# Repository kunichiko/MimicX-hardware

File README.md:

# MimicX-hardware

**製品名: Mimic X** — 「Mimic X」プロジェクトのマイコン基板設計データ。

*Mimic X is an open-hardware USB-MIDI adapter family that lets a phone (or any
USB-MIDI / BLE-MIDI host) drive the real peripheral ports of 1980s Japanese
computers — the Sharp X68000 keyboard/mouse port and the ATARI-standard
9-pin joystick port, including Mega Drive 6-button pads. This repository holds
the board designs; the firmware, the protocol spec and the phone app live in the
sibling repositories linked at the bottom.*

- **Licence**: **CERN-OHL-S-2.0** (see [`LICENSE`](LICENSE)) — the `.ato`
  sources, the KiCad layouts and the docs are all modifiable sources.
  `tools/` is Apache-2.0. Vendor-supplied symbols, footprints and 3D models
  under `<board>/parts/` are third-party and are **not** covered; see
  [`NOTICE`](NOTICE) for the exact carve-out, the trademark terms and the
  datasheet policy.
- **MCU**: WCH **CH32X035G8U6** (QFN-28, RISC-V, 48 MHz, native USB 2.0 FS).
- **USB VID:PID**: `0x1209:0x9210` (Mimic X) and `0x1209:0x9211` (Mimic X
  Bridge), [requested from pid.codes](https://github.com/pidcodes/pidcodes.github.com/pull/1210).
- **Designed in [atopile](https://atopile.io)** — see
  [Design sources](#design-sources--回路図ファイルが無い理由) for why there is
  no `.kicad_sch` and where to read the circuit instead.

## 基板バリエーション / Boards

### `atari-joystick/` — ATARI / X68000 ジョイスティックアダプタ

D-SUB 9pin メス。X68000 / ATARI 標準ポートに直挿しし、メガドライブ 6 ボタン
パッドもエミュレートする。**rev 1.0.0、JLCPCB で製造済み。**

<p align="center"><sub>実装済みの基板と 3D プリントのケース (左) / KiCad レイアウトの 3D レンダ (右)。裏面と拡大は <a href="atari-joystick/README.md">基板 README</a> を参照</sub></p>

| | |
|---|---|
| ブロック図 / block diagram | [PDF](atari-joystick/docs/atari-joystick-block-diagram.pdf) · [SVG](atari-joystick/docs/atari-joystick-block-diagram.svg) |
| PCB レイヤープロット / layer plots | [PDF](atari-joystick/docs/atari-joystick-pcb.pdf) (silk / Cu / fab, 6 pages) |
| 対話的に眺める / browse the layout | [KiCanvas](https://kicanvas.org/?repo=https%3A%2F%2Fgithub.com%2Fkunichiko%2FMimicX-hardware%2Fblob%2Fmain%2Fatari-joystick%2Flayouts%2Fdefault%2Fdefault.kicad_pcb) |
| 回路の定義 / circuit source | [`atari_joystick.ato`](atari-joystick/atari_joystick.ato) |
| 製造データ / fabrication | [`layouts/default/production/`](atari-joystick/layouts/default/production) (Gerber + BOM + CPL) |
| 設計メモ / design notes | [`README.md`](atari-joystick/README.md) |

### `x68000-keyboard/` — X68000 キーボード / マウスアダプタ

ミニ DIN 7pin オス。X68000 のキーボード端子はマウス端子を兼用しており、本基板も
1 コネクタで両方をエミュレートする。4 層。**rev 1.0.0、JLCPCB で製造済み。rev 1.0.1 (外形のセンターずれ修正) は未発注。**

<p align="center"><sub>実装済みの基板と 3D プリントのケース (左) / KiCad レイアウトの 3D レンダ (右)。裏面と拡大は <a href="x68000-keyboard/README.md">基板 README</a> を参照</sub></p>

| | |
|---|---|
| ブロック図 / block diagram | [PDF](x68000-keyboard/docs/x68000-keyboard-block-diagram.pdf) · [SVG](x68000-keyboard/docs/x68000-keyboard-block-diagram.svg) |
| PCB レイヤープロット / layer plots | [PDF](x68000-keyboard/docs/x68000-keyboard-pcb.pdf) (silk / Cu ×4 / fab, 8 pages) |
| 対話的に眺める / browse the layout | [KiCanvas](https://kicanvas.org/?repo=https%3A%2F%2Fgithub.com%2Fkunichiko%2FMimicX-hardware%2Fblob%2Fmain%2Fx68000-keyboard%2Flayouts%2Fdefault%2Fdefault.kicad_pcb) |
| 回路の定義 / circuit source | [`x68000_keyboard.ato`](x68000-keyboard/x68000_keyboard.ato) |
| 製造データ / fabrication | [`layouts/default/production/`](x68000-keyboard/layouts/default/production) (Gerber + BOM + CPL) |
| 設計メモ / design notes | [`README.md`](x68000-keyboard/README.md) |

### `wireless-combo/` — 無線 (BLE-MIDI) Combined アダプタ

XIAO ESP32-C6 (BLE-MIDI ホスト) + CH32X035 (デバイスエンジン) の 2 チップ構成で、
ジョイスティックとキーボードの両ポートを 1 枚で担当する。ESP32 が CH32 の電源と
BOOT ピンを握っているため、CH32 のファームが壊れても SWD 経由で自力復旧できる。

> **rev 0.1 — 配線済み (4 層、DRC クリーン)、未発注。** 3D レンダと
> レイヤープロットはまだ置いていない。回路の全体像はブロック図と `.ato` を参照。

| | |
|---|---|
| ブロック図 / block diagram | [PDF](wireless-combo/docs/wireless-combo-block-diagram.pdf) · [SVG](wireless-combo/docs/wireless-combo-block-diagram.svg) |
| 回路の定義 / circuit source | [`wireless_combo.ato`](wireless-combo/wireless_combo.ato) |
| 設計メモ / design notes | [`README.md`](wireless-combo/README.md) |

## Design sources / 回路図ファイルが無い理由

この 3 基板はいずれも **[atopile](https://atopile.io) で設計している**。atopile は
回路を「図」ではなく「コード」で書く EDA で、`.ato` から直接ネットリストと KiCad
レイアウトを生成する。したがって **プロットできる回路図シート (`.kicad_sch`) は
そもそも存在しない**。回路を読むには次のいずれかを使う:

*These boards are designed in atopile, a text-based EDA: the circuit is written
as code and the netlist and KiCad layout are generated from it. There is no
schematic sheet to plot, so a reviewer has three ways in instead:*

1. **ブロック図 PDF** (`<board>/docs/*-block-diagram.pdf`) — 全ブロック、全信号、
   電源ドメイン、ピン割当表を 1 枚に収めた図。`tools/gen_block_diagrams.py` で
   生成しており、内容は `.ato` の記述と 1:1 で対応する。
   *The closest thing to a schematic: every block, every net that leaves a
   block, the power domains and the full pin map on one A4 sheet.*
2. **`.ato` ソース** — 部品・接続・値・設計理由がコメント付きで書かれている
   一次情報。`~` が接続、`~>` が直列挿入を表す。
   *The primary source, with the reasoning in the comments.*
3. **KiCad レイアウト** (`<board>/layouts/default/default.kicad_pcb`) — 上の表の
   KiCanvas リンクからブラウザで開ける。ネット名は `.ato` 側で
   `has_net_name` により意味のある名前 (`UP_3V3`, `KEY_TXD_3V3` など) に固定済み。
   *Browsable in KiCanvas; the nets carry meaningful names, not `Net-(U1-Pad3)`.*

ブロック図とレイヤープロットの再生成:

```sh
# ブロック図 (SVG + PDF)。PDF は headless Chrome で出力する
python3 tools/gen_block_diagrams.py

# PCB レイヤープロット
KC=/Applications/KiCad/KiCad.app/Contents/MacOS/kicad-cli
$KC pcb export pdf --mode-multipage \
   --layers F.Silkscreen,F.Cu,B.Cu,B.Silkscreen,F.Fab,Cmts.User \
   --common-layers Edge.Cuts \
   -o atari-joystick/docs/out atari-joystick/layouts/default/default.kicad_pcb
```

## 共通設計事項

- **MCU**: CH32X035G8U6 (QFN-28、48MHz、USB Full-Speed 内蔵)。**5V トレラント
  ではない** (絶対最大定格 VIN ≤ VDD+0.3V) ため、ターゲット機の 5V 信号とは
  必ずレベルシフタ (TC7MPB9307FT, パッシブ FET バススイッチ) を介して接続する
- **USB**: Type-C Receptacle、CC1/CC2 にそれぞれ 5.1kΩ プルダウン (Rd = sink/UFP)。
  CC は MCU の PC14/PC15 にも引いて内蔵 USB-PD コントローラで直接サンプリングする
- **電源**: USB バスパワー (VBUS 5V) を LDO (LP5907MFX-3.3) で 3.3V に降圧して MCU に
  供給する。CH32X035 の USB トランシーバ出力は VDD 直結なので、規格準拠ホストと
  正しく enumerate させるため VDD は必ず 3.3V にする。ターゲット機からの 5V は
  レベルシフタの B 側電源としてのみ使い、VBUS とは基板内で分離して逆流を防ぐ
- **デカップリング**: VDD ピンに 4.7µF + 0.1µF を近接配置
- **表示**: 電源 LED (緑 0603、常時点灯) + フルカラー LED (WS2812B-2020、
  DI 直前に 470Ω 直列ダンピング抵抗)。atari-joystick 以外の基板は 3.3V 給電が
  定格内の同外形品 WS2812B-2020-V6 (C52917434) に置き換え済み
- **書き込み**: BOOT ボタンで PC17 (USB D+) を 4.7kΩ 経由で HIGH に引き上げた状態で
  リセットすると、WCH の USB DFU ブートローダに入る

## 関連リポジトリ / Related repositories

- [MimicX-app](https://github.com/kunichiko/MimicX-app) — Flutter アプリ (USB-MIDI / BLE-MIDI ホスト)
- [MimicX-firmware](https://github.com/kunichiko/MimicX-firmware) — マイコンファームウェア (CH32X035 / ESP32)
- [MimicX-protocol](https://github.com/kunichiko/MimicX-protocol) — USB-MIDI 通信プロトコル仕様

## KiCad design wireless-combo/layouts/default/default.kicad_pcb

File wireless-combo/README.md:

# MimicX Wireless Combo Adapter (XIAO ESP32-C6 + CH32X035)

*BLE-MIDI wireless Combined adapter: an ESP32-C6 takes MIDI in over BLE or USB
and relays it to a CH32X035 device engine over I2C, driving both retro ports
from one board. **Board rev 0.1 — routed (4-layer, DRC clean), not yet
fabricated**; renders and layer plots are not here yet. Designed in
[atopile](https://atopile.io); the circuit lives in
[`wireless_combo.ato`](wireless_combo.ato).*

- **ブロック図 / block diagram**:
  [PDF](docs/wireless-combo-block-diagram.pdf) ·
  [SVG](docs/wireless-combo-block-diagram.svg)
- **USB VID:PID**: `0x1209:0x9211` (Mimic X Bridge — 無線側は ESP32 が USB
  デバイスとして見えるため、有線 2 基板とは別 PID)

BLE-MIDI 無線対応の Combined アダプタ。1 枚の基板に

- **Seeed XIAO ESP32-C6** — BLE-MIDI ホスト / CH32 の自動 OTA (SWD) / 電源・BOOT 制御
- **CH32X035G8U6** — デバイスエンジン (`combined-i2c` ファーム)
- **2x5 ボックスヘッダ** — フラットケーブル経由で D-SUB 9pin (ATARI / X68000 / MD ジョイスティック)
- **2x4 ボックスヘッダ** — フラットケーブル経由で Mini DIN 7pin (X68000 キーボード / マウス / REMOTE)
- **JST XH 3P** — WCH-LinkE 用 SWD デバッグ端子 (保険)
- **M3 ネジ穴 ×4** — メッキ穴、GND 接続 (ケース固定用)

D-SUB / Mini DIN は基板直付けせず、2.54mm ボックスヘッダ (逆挿し不可) 経由の
汎用フラットケーブル接続とする。2x5 側は IDC 圧着型 D-SUB 9pin をそのまま
圧着したケーブルが使える配列にしてある。

を搭載する。ファームウェアは既存の 2 チップ構成 (protocol §2.5) をそのまま使う:
CH32 側 = `MimicX-firmware/platforms/ch32x035` の `combined-i2c` env、
ESP32 側 = `MimicX-firmware/platforms/esp32c6` (内包イメージを `mimic-x-combo` に設定)。

## ブロック図

```
                USB-C (給電 + 書込/ログ)
                   │
  ┌────────────────┴───┐        VDD33 (常時)
  │  XIAO ESP32-C6     │3V3 ──┬─────────────┐
  │                    │      │             S│
  │ D0: CH32_PWR_OFF ──┼──────┼──────────── G│Q1 AO3401A (default ON)
  │ D1: CH32_BOOT ─────┼─4.7k─┼─┐           D│
  │ D3: CH32_INT ──────┼──┐   │ │   VDD_SW ──┴─┬──[10k]── GND (ブリーダ)
  │ D4: SDA_SWDIO ─────┼─┐│   │ │      │       │
  │ D5: SCL_SWCLK ─────┼┐││ [pull-ups 4.7k/10k は VDD_SW へ]
  └────────────────────┘│││   │ │      │
                        │││   │ │  ┌───┴──────────┐    ┌─ TC7MPB9307FT ─ D-SUB9
             PC19/SCL ──┘││   │ └──│ PC17 (BOOT)  │────┤   (VCCB = D-SUB Pin5)
             PC18/SDA ───┘│   │    │  CH32X035    │    │
             PB1/INT ─────┘   │    │ combined-i2c │    └─ TC7MPB9307FT ─ MiniDIN7
                              │    │   PB0 ─ WS2812B    (VCCB = DIN Pin1 Vcc2)
              BOOTボタン ─4.7k┴────│              │
                                   └──────────────┘
```

## この基板の設計肝: ESP32 による CH32 の電源 / BOOT 制御

既存構成の弱点は「CH32 ファームが起動直後に SDI (SWD) を無効化するため、
I2C が死ぬと SWD でも復旧できない半ブリック状態が生じる」こと (実事例あり)。
本基板は WCH ISP ブートローダが SDI を有効のまま残すこと (実機検証済み) を
利用し、ESP32 の GPIO 2 本で **どんなファーム状態からでも** 復旧できる:

| XIAO ピン | GPIO | 機能 | 極性 |
|---|---|---|---|
| D0 | GPIO0 | `CH32_PWR_OFF` — Q1 ゲート | High=電源OFF (100k PD でデフォルトON) |
| D1 | GPIO1 | `CH32_BOOT` — 4.7k 経由で PC17(UDP) | POR 時 High=ブートローダ突入 |
| D3 | GPIO21 | `CH32_INT` (既存) | active-low, 10k PU→VDD_SW |
| D4 | GPIO22 | `SDA_SWDIO` (既存) | 4.7k PU→VDD_SW |
| D5 | GPIO23 | `SCL_SWCLK` (既存) | 4.7k PU→VDD_SW |

### 復旧シーケンス (ESP32 ファームに実装する)

```
1. SDA/SCL/INT/BOOT を Low 出力 or プルなし Hi-Z にする
   (OFF 中に 1 本でも High があると保護ダイオード経由のバックフィードで
    POR がかからない。プルアップ類を VDD_SW に繋いでいるのも同じ理由)
2. CH32_PWR_OFF = High → 100ms 待つ (10k ブリーダで VDD_SW 放電)
3. CH32_BOOT = High
4. CH32_PWR_OFF = Low → POR。PC17=High でブートローダ突入 (SDI 有効)
5. ~50ms 後 CH32_BOOT = Low (書込後の ndmreset でアプリ起動させるため)
6. 即 SWD 書込 (ブートローダのタイムアウト前に halt すれば以降は安全)
```

`ch32_ota.c` の SWD 失敗時フォールバックとしてこのシーケンスを足せば、
ENTER_SWD ハンドオフ (CH32 ファームの協力前提) に依存しない自己修復になる。

## 電源設計

5V 電源は 3 系統あり、**どれか 1 つでも供給されていれば動作する**:

```
USB-C (XIAO) ──────────────────┬── VCC_ESP (5V 幹線 = XIAO 5V ピン)
VCC_JOY (D-SUB Pin5) ─▶|B5819W─┤        │ XIAO 内蔵 LDO
VCC_KBD (DIN Pin1)   ─▶|B5819W─┘        ▼
                                      VDD33 (3.3V 常時系)
                                        │ Q1 (P-FET)
                                        ▼
                                      VDD_SW (CH32 サブシステム)
```

- XIAO の 3V3 ピンは内蔵 LDO の**出力** (入力不可)。USB 未接続時はホスト 5V を
  ショットキー経由で 5V ピン (VBUS) に注入して XIAO を駆動する (Seeed 公式推奨方式)
- 回路全体の 3.3V は XIAO 内蔵 LDO 出力 (`VDD33`) を使う。CH32 サブシステムの
  追加負荷は最悪 ~60mA 程度 (CH32 ~10mA + WS2812 ≤45mA + プルアップ) で、
  ESP32 自身の無線ピークを賄う前提の内蔵レギュレータの範囲内。
  ノイズや電流に不安が出た場合は VCC_ESP → 外付け 3.3V レギュレータで
  ESP32 以外の 3.3V を分離する代替案あり (既存基板の LP5907MFX-3.3 は 250mA で
  この用途には十分。ただし ESP32 本体は駆動できない点に注意)
- B5819W (SOD-123, LCSC C8598) の Vf は 0.3A 付近で 0.4V 台 → ホスト給電時 VCC_ESP ≈ 4.5〜4.6V。ダイオードにより
  VCC_JOY / VCC_KBD は相互に直結されず、USB VBUS からホストへの逆流もない
- ホスト給電時は ESP32 の無線 TX バースト (数百 mA) がレトロ機のポート給電に
  乗る。VCC_ESP に 22µF バルクを置いて平滑しているが、**ホスト側ポートの
  給電能力 (ヒューズ/許容電流) は実機で要確認**
- CH32 サブシステム (CH32 / WS2812 / プルアップ / レベルシフタ VCCA) は
  すべて `VDD_SW` (Q1 スイッチド)。**このレールに載せ忘れた常時系プルアップが
  1 本でもあると電源 OFF 復旧が壊れる**ので、変更時は要注意
- レベルシフタ B 側 (5V) はホスト給電: `VCC_JOY` (D-SUB Pin5) と
  `VCC_KBD` (DIN Pin1 Vcc2) を各コネクタから直接取る
- CH32 の USB は未接続 (PC16 = NC, PC17 = BOOT 制御専用)。最終復旧手段も
  ESP32 経由の BOOT+SWD で代替できるため、wchisp 用 USB は設けない

## ケーブル配線 (ヘッダ Pin n = フラットケーブルの芯線 n)

専用の[変換基板](#変換基板-atari-joystick-bo--x68000-keyboard-bo)を使う場合は、両端とも IDC ソケットを
同じ向き (1 番線 = ▽ 側) に圧着したストレートケーブルでつなぐ。以下は変換基板を
使わずにケーブル側で直接コネクタを付ける場合の対応表。

| 2x5 (J: joystick) | D-SUB 9pin | | 2x4 (J: keyboard) | Mini DIN 7pin |
|---|---|---|---|---|
| 1 | 1 Up | | 1 | 1 Vcc2 (+5V) |
| 2 | 6 TRIG-A | | 2 | 2 MSDATA |
| 3 | 2 Down | | 3 | 3 KEY RxD |
| 4 | 7 TRIG-B | | 4 | 4 KEY TxD |
| 5 | 3 Left | | 5 | 5 READY |
| 6 | 8 COMMON / TH | | 6 | 6 REMOTE |
| 7 | 4 Right | | 7 | 7 GND (シールドもここへ) |
| 8 | 9 GND | | 8 | GND (予備) |
| 9 | 5 +5V (ホスト給電) | | | |
| 10 | GND (D-SUB 側は未接続) | | | |

- **ジョイスティック**: 10 芯フラットケーブルの片側に 2x5 IDC ソケット、反対側に
  **IDC 圧着型 D-SUB 9pin メス** を (1 番線 = D-SUB Pin1 に合わせて) 圧着するだけ
  でよい。IDC D-SUB は芯線を 1→1, 2→6, 3→2 … と上下段に交互に振り分けるため、
  上表のヘッダ配列になっている (PC のシリアルポート用ブラケットケーブルと同じ
  "AT/Intel" 配列)。10 番線 (基板側 GND) は D-SUB 側で未接続
- **キーボード**: IDC 圧着型の Mini DIN は無いので、8 芯フラットケーブルの片側に
  2x4 IDC ソケットを圧着し、反対側は芯線 1〜7 を DIN プラグの同番ピンへ手配線する。
  DIN シールドは**ケーブル側コネクタの根元で GND (7 番線) に合流**させる
- 10P ソケットは 8P ヘッダに入らないが、8P ソケットは 10P ヘッダのシュラウドに
  片寄せで入ってしまう場合があるので、ケーブルにはラベルを付けておく
- 基板側: 2x5 ボックスヘッダ BOOMELE 2.54-2\*5P = LCSC C5665、
  2x4 ボックスヘッダ BOOMELE 2.54-2\*4P = LCSC C9135

## 変換基板 (atari-joystick-bo / x68000-keyboard-bo)

フラットケーブルの先に付ける受動基板。同じ atopile プロジェクトの別ビルドとして
持ち、ボックスヘッダは親基板と同じ `parts/idc_connectors.ato` の定義を使う
(ピン配置が親子で食い違わない)。ビルド名の `-bo` は breakout の略。将来ほかの
ジョイスティックや機種 (PC-98 キーボードなど) 用を足せるよう、対象機の名前を前に付けている。

| ビルド | エントリ | レイアウト | 構成 | 形状 |
|---|---|---|---|---|
| `atari-joystick-bo` | [`atari_joystick_bo.ato`](atari_joystick_bo.ato) | `layouts/atari-joystick-bo/` | J1: 2x5 ボックスヘッダ (C5665) / J2: ハンダカップ型 D-SUB 9pin メス用エッジパッド (手はんだ) | atari-joystick-slim 形 35 × 16 mm |
| `x68000-keyboard-bo` | [`x68000_keyboard_bo.ato`](x68000_keyboard_bo.ato) | `layouts/x68000-keyboard-bo/` | J1: 2x4 ボックスヘッダ (C9135) / J2: Mini DIN 7pin オス (手はんだ) | x68000-keyboard 形 (本体 20.6 × 12.2 mm) |

- どちらも 2 層、厚さ **1.6 mm** (D-SUB のハンダカップ列の間に入る厚み)
- コネクタ側は元の基板と同寸 (atari-joystick-bo: 先端 10 mm のエッジパッドと M2.6 用
  φ2.8 穴 ×2、x68000-keyboard-bo: ネックと Mini DIN まわり)。ボックスヘッダを載せるため
  後ろ側を延長してある (atari-joystick-bo +5 mm、x68000-keyboard-bo +6.4 mm)
- D-SUB の取り付け方は [atari-joystick-slim の README](../atari-joystick-slim/README.md#d-sub-9pin-の取り付け) と同じ
- 状態: 配線済み、未発注

### SWD デバッグ端子 (XH 3P, B3B-XH-A = LCSC C144394)

WCH-LinkE でのデバッグ / 強制書き換え用の保険。PC18/PC19 は I2C/SWD 兼用線
なので実体は I2C バスのタップ。
**通常は未実装** (BOM / CPL から除外済み)。使うときだけ B3B-XH-A を手はんだする。

| XH 3P | 信号 |
|---|---|
| 1 | SWCLK (= SCL, CH32 PC19) |
| 2 | SWDIO (= SDA, CH32 PC18) |
| 3 | GND |

使用時の注意:
- ESP32 が同じ線を駆動するため、**WCH-LinkE 使用中は ESP32 を静かにしておく**
  (リセット保持、または I2C/OTA が走っていないタイミングで)
- 通常稼働中の CH32 は SDI off なので、**BOOT ボタン + 電源再投入でブート
  ローダ (SDI 有効) にしてから**繋ぐと確実

## 実装前 TODO

- [ ] `parts/XIAO_ESP32C6/` のフットプリントは**仮置き** (2.54mm ピッチ /
      列間 15.24mm)。Seeed 公式の機械図面と照合して確定させる
- [ ] `parts/AO3401A_SOT23/` の SOT-23 ランド、`parts/B5819W_SOD123/` の SOD-123 ランド (KiCad 標準)、
      `parts/JST_XH_B3B/` の XH ランドを
      データシート推奨値と照合
- [ ] 信号ラインの TVS (SP3012-04UTG 等) 追加検討 — ケーブル化で配線が伸びる
      ため既存基板より優先度高
- [ ] 10kΩ / 100kΩ 抵抗は初回 `ato build` 時に LCSC ピッカーが解決する
      (ネットワーク必要)。他はローカル parts/ キャッシュで完結
- [ ] ESP32 ファームに `CH32_PWR_OFF` / `CH32_BOOT` の制御と復旧フォール
      バックを実装 (`board_config.h` に BOARD_CH32_PWR_GPIO=0 /
      BOARD_CH32_BOOT_GPIO=1 を追加)

## ビルド

```sh
cd MimicX-hardware/wireless-combo
~/.local/bin/ato build --keep-picked-parts               # 3 基板すべて
~/.local/bin/ato build --keep-picked-parts -b atari-joystick-bo   # 1 基板だけ (default / atari-joystick-bo / x68000-keyboard-bo)
```

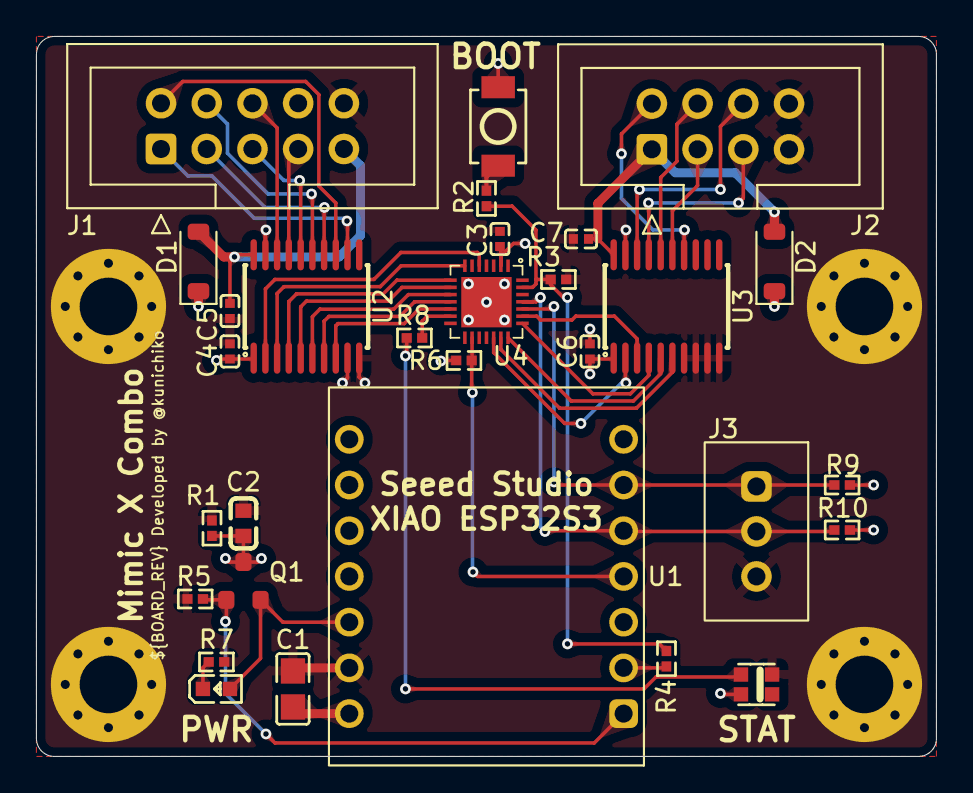
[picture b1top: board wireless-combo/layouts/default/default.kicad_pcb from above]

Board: 4 copper layers, 50.0 x 40.0 mm, 34 parts (0 on the bottom side), 40 nets.

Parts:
C1: 22µF ±20%; C0805
C2: 4.7µF ±10%; C0603
C3, C4, C5, C6, C7: 100nF ±10%; C0402
D1, D2: B5819W_SOD123
H1, H2, H3, H4: MountingHole_M3
J1: IDC_Header_2x05
J2: IDC_Header_2x04
J3: JST_XH_B3B
LED1: LED0603-RD
LED2: LED-SMD_4P-L2.2-W2.0-P1.00_WS2815C-2020-4P
Q1: AO3401A_SOT23
R1, R6: 10kΩ ±1%; R0402
R2, R4, R9, R10: 4.7kΩ ±1%; R0402
R3, R5: 100kΩ ±1%; R0402
R7: 1kΩ ±1%; R0402
R8: 470Ω ±1%; R0402
SW1: SW-SMD_L3.9-W3.0-P4.45
U1: XIAO_ESP32C6
U2, U3: TSSOP-20_L6.5-W4.4-P0.65-LS6.5-BL
U4: QFN-28_L4.0-W4.0-P0.40-BL-EP2.8

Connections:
CH32_BOOT: R4.1, U1.2
CH32_INT: R6.2, U1.4, U4.16
CH32_PWR_OFF: Q1.1, R5.1, U1.1
COMMON_3V3: U2.2, U4.5
DOWN_3V3: U2.6, U4.10
GND: C1.2, C2.2, C3.2, C4.2, C5.2, C6.2, C7.2, H1.1, H2.1, H3.1, H4.1, J1.8, J1.10, J2.7, J2.8, J3.3, LED2.2, R1.2, R3.2, R5.2, R7.2, U1.13, U2.9, U2.10, U2.19, U3.7, U3.8, U3.9, U3.10, U3.19, U4.29
KEY_RXD_3V3: U3.5, U4.21
KEY_TXD_3V3: U3.4, U4.22
LEFT_3V3: U2.4, U4.8
MSDATA_3V3: U3.6, U4.20
PB0: R8.1, U4.13
READY_3V3: U3.3, U4.23
REMOTE_3V3: U3.2, U4.19
RIGHT_3V3: U2.3, U4.7
SCL_SWCLK: J3.1, R9.2, U1.6, U4.24
SDA_SWDIO: J3.2, R10.2, U1.5, U4.25
TRIGA_3V3: U2.7, U4.11
TRIGB_3V3: U2.5, U4.9
UP_3V3: U2.8, U4.12
VCC_ESP: C1.1, D1.1, D2.1, U1.14
VCC_JOY: C5.1, D1.2, J1.9, U2.20
VCC_KBD: C7.1, D2.2, J2.1, U3.20
VDD33: LED1.2, Q1.2, U1.12
VDD_SW: C2.1, C3.1, C4.1, C6.1, LED2.4, Q1.3, R1.1, R6.1, R9.1, R10.1, SW1.1, U2.1, U3.1, U4.2
cathode: LED1.1, R7.1
common: J1.6, U2.18
din: LED2.3, R8.2
down: J1.3, U2.14
key_rxd: J2.3, U3.15
key_txd: J2.4, U3.16
left: J1.5, U2.16
msdata: J2.2, U3.14
ready: J2.5, U3.17
remote: J2.6, U3.18
right: J1.7, U2.17
terminal_b: R2.1, SW1.2
triga: J1.2, U2.13
trigb: J1.4, U2.15
up: J1.1, U2.12
usb_dp: R2.2, R3.1, R4.2, U4.27

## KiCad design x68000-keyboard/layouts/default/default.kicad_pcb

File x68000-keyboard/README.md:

# x68000-keyboard

Mimic X — X68000 キーボードアダプタ基板 (キーボード + マウス相乗り対応)

*USB-MIDI to Sharp X68000 keyboard/mouse port adapter (mini-DIN 7P, 4-layer
board). Board rev 1.0.0 fabricated at JLCPCB; rev 1.0.1 (outline centering fix)
not yet ordered. Designed in
[atopile](https://atopile.io) — the circuit lives in
[`x68000_keyboard.ato`](x68000_keyboard.ato), not in a schematic sheet.*

<p align="center"><sub>実装済みの基板と 3D プリントのケース (背景はカッティングマット)</sub></p>

<p align="center"><sub>KiCad レイアウトの 3D レンダ (部品面 / はんだ面)</sub></p>

- **ブロック図 / block diagram**:
  [PDF](docs/x68000-keyboard-block-diagram.pdf) ·
  [SVG](docs/x68000-keyboard-block-diagram.svg) — 全ブロック・全信号・電源
  ドメイン・ピン割当を 1 枚に収めた図
- **PCB レイヤープロット / layer plots**:
  [PDF](docs/x68000-keyboard-pcb.pdf) (silk / Cu ×4 / fab, 8 pages)
- **レイアウトをブラウザで**:
  [KiCanvas](https://kicanvas.org/?repo=https%3A%2F%2Fgithub.com%2Fkunichiko%2FMimicX-hardware%2Fblob%2Fmain%2Fx68000-keyboard%2Flayouts%2Fdefault%2Fdefault.kicad_pcb)
- **製造データ**: [`layouts/default/production/`](layouts/default/production)
  (Gerber + BOM + CPL, JLCPCB 発注そのまま)
- **USB VID:PID**: `0x1209:0x9210`

## 用途

スマートフォン (USB-MIDI ホスト) から CH32X035 経由で、X68000 のキーボード
信号 (KEY TxD/RxD) およびマウス信号 (MSDATA) を生成し、X68000 本体の
ミニ DIN 7pin ポートに接続して使用する。

X68000 のキーボードコネクタは **マウス端子を兼用** しており、本基板も
1 つのコネクタで両方をエミュレートする (ファーム `BOARD_X68K_FULL`)。

## 主要部品

| 部品 | 型番 / 仕様 | 備考 |
|------|-----------|------|
| MCU | WCH CH32X035G8U6 | QFN28、48MHz、USB Full-Speed 内蔵、3.3V 駆動 |
| USB コネクタ | USB Type-C (Receptacle, 16pin) | スマートフォンと接続 |
| 出力コネクタ | Mini DIN 7pin オス (自作 `MiniDIN_7P_X68000`) | X68000 キーボード端子 (手配コネクタを基板に直付け) |
| LDO | LP5907MFX-3.3 (250 mA) | VBUS 5V → MCU VDD 3.3V |
| レベルシフタ | Toshiba TC7MPB9307FT (TSSOP-20) | 8-bit Dual-Supply Bus Switch、3.3V↔5V |
| BOOT ボタン | XUNPU TS-1088-AR02016 (3.9×3.0mm, 2 ピン) | リセット時 USB DFU 起動用 |
| その他 | デカップリング 0.1µF / 4.7µF, USB Type-C CC 抵抗 5.1kΩ ×2 |

> 基板上の状態表示は **電源 LED (緑 0603, 常時点灯)** と **フルカラー LED
> (WS2812B-2020-V6, シリアル制御 RGB)** の 2 個。PB3 / PB4 は引き続き未使用。

## ピン割当 (CH32X035G8U6 QFN28 → コネクタ)

> **注意 (重要)**: 旧版 README には `PA15–PA19` という記載があったが、これは
> CH32X035 別パッケージ (LQFP48 など) のピン名で、MimicX で採用している
> **CH32X035G8U6 (QFN28) には存在しない**。詳細は `../docs/CH32X035.md` §3 参照。
> 以下が QFN28 の実ピンに合わせた最新割当。

| QFN28 Pin | MCU 信号 | レベルシフタ | DIN 7pin | 方向 (MCU 視点) | 用途 |
|---:|---|---|---:|---|---|
| 22 | PB11 (USART1_RX, RX1_2) | a6↔b6 | Pin 4 (KEY TxD) | **IN** | X68000 本体からのコマンド受信 (2400/8N1) |
| 21 | PB10 (USART1_TX, default) | a4↔b4 | Pin 3 (KEY RxD) | **OUT** | キーコード送信 (2400/8N1) |
| 23 | PB12 (GPIO 入力) | a5↔b5 | Pin 5 (READY) | IN | 1=ホスト準備完了、Low 時送信抑止 |
| 20 | PB9 (USART4_TX, TX4_3) | a8↔b8 | Pin 2 (MSDATA) | OUT | マウスデータ送信 (4800/8N2) |
| 19 | PB8 (GPIO) | a7↔b7 | Pin 6 (REMOTE) | (FW 依存) | TV リモコン信号。用途は将来検討 |
| 13 | PB0 | — | — | OUT | フルカラー LED (WS2812B-2020-V6) DI 駆動。470Ω 直列ダンピング抵抗経由 |
| 14 | PB3 | — | — | — | 未使用 |
| 15 | PB4 | — | — | — | 未使用 |
| —  | (GND) | — | Pin 7 | — | 共通 GND |
| —  | (VCC2) | (B 側 VCCB) | Pin 1 (Vcc2 +5V) | — | X68000 本体の +5V をレベルシフタ B 側電源として受け入れ |

USART のリマップ設定 (`AFIO_PCFR1`):
- `USART1` は PB10/PB11 を使うため `USART1_REMAP` ビットの設定で
  `RX1_2` (= PB11) にマップする必要がある。
- `USART4` は PB9 の `TX4_3` リマップを使用 (MSDATA は送信のみで RX は不要)。

詳細はファームウェア `MimicX-firmware/src/functions/x68k_keyboard/` および
`x68k_mouse/` 参照。

## DIN ピン名の方向解釈 (重要)

X68000 サービスマニュアル上の `KEY TxD` / `KEY RxD` は **X68000 本体 (ホスト) 視点**
で命名されている:

| Pin | ラベル | データの流れ | MCU (= キーボード側) の動作 |
|----:|---|---|---|
| 3 | KEY RxD | ホストが**受信** ← キーボード | MCU は**送信** (TX) |
| 4 | KEY TxD | ホストが**送信** → キーボード | MCU は**受信** (RX) |

UART の一般則「片側の Tx は相手側の Rx に繋ぐ」を素直に適用すれば良い:
- ホストの TxD (Pin 4) → MCU の RX1 (PB11)
- ホストの RxD (Pin 3) ← MCU の TX1 (PB10)

## ミニ DIN 7pin (本体側 = メス、当基板側 = オス)

```
       _______
      /  4 3  \         (DIN 7pin Male, looking at the plug from outside)
     | 7  6  5 |
      \_2 1__/
```

本基板は **ユーザ手配のコネクタを直接はんだ付け** する想定で、フットプリントは
自作 (`parts/MiniDIN_7P_X68000/MiniDIN_7P_X68000.kicad_mod`) を採用している。
コネクタの実寸 (Hirose HMD-7P 系を想定) に合わせて KiCad の Footprint Editor
で本実装済み。差し替える場合は同ファイルを編集して `ato build` を再実行する。
X68000 サービスマニュアル準拠のピン配置:

| Pin | 信号 | 当基板での扱い |
|-----|------|---|
| 1 | Vcc2 (+5V) | レベルシフタ B 側 VCCB に接続 (X68000 から給電) |
| 2 | MSDATA (キーボード→本体) | MCU PB9 ← レベルシフタ |
| 3 | KEY RxD (キーボード→本体) | MCU PB10 (TX1) ← レベルシフタ |
| 4 | KEY TxD (本体→キーボード) | MCU PB11 (RX1) ← レベルシフタ |
| 5 | READY (本体→キーボード) | MCU PB12 ← レベルシフタ |
| 6 | REMOTE (TV リモコン用) | MCU PB8 ← レベルシフタ |
| 7 | GND | 共通 GND |

## 信号レベルとバッファ

- すべて **5V TTL**
- CH32X035 は **5V トレラントではない** (絶対最大定格 VIN ≤ VDD+0.3V =
  3.6V at VDD=3.3V)。詳細は `../docs/CH32X035.md` §5・§7 参照。
- そのため X68000 側 5V 信号と接続する全 5 ラインに **Toshiba TC7MPB9307FT
  (8 ch パッシブ FET バススイッチ、TSSOP-20)** を介す。
  - VCCA = VDD33 (3.3V、MCU 側) / VCCB = VCC2 (5V、X68000 本体の Vcc2) / OE = GND 固定
  - チャネル 4〜8 を使用 (a4/a5/a6/a7/a8)、未使用の 1〜3 は A 側を GND に落としてフローティング回避
- パッシブ FET 型 (FET パススルー) を選定する理由は ATARI アダプタと同じで、
  X68000 ホスト側 8255 + プルアップとの相性を考慮したもの。`../docs/CH32X035.md`
  §7 参照。

## 電源

本基板は **2 系統の電源** を用途別に取り込む構成:

| レール | 供給元 | 用途 |
|---|---|---|
| **VBUS (5V)** | USB Type-C (スマホ等のホスト) | LDO で 3.3V に降圧して MCU と レベルシフタ A 側 (VCCA) を駆動 |
| **VDD33 (3.3V)** | LDO (LP5907MFX-3.3) | MCU 本体・LDO 後段デカップリング |
| **VCC2 (5V)** | X68000 本体 DIN Pin 1 (Vcc2) | レベルシフタ B 側 (VCCB) — 5V 信号レベル基準と同電位を取る |

ポイント:
- VBUS と Vcc2 は基板上で **直接接続しない** (それぞれ別のレールとして分離)。
  逆流・逆給電のリスクが無くなる。
- レベルシフタ B 側電源を X68000 側 5V (Vcc2) から取ることで、ホスト側信号
  レベルと完全に整合する (ホストが電源断のときは B 側も電位がなくなるので、
  バススイッチが自然と high-Z 状態になる)。
- MCU 動作には USB 接続が必須 (スマホからのバスパワー 5V → LDO で 3.3V)。
  X68000 単体で電源を取って動作させたい場合は本構成では非対応。

## レイアウトのヒント

- USB Type-C コネクタは基板の一辺に
- ミニ DIN 7pin は反対側エッジ。X68000 本体への取り回しを想定して
  ケーブル方向を考える
- QFN28 周りはデカップリング (4.7µF + 0.1µF) を近接配置
- USB 信号 (DP/DM) は 90Ω 差動でルーティング
- KEY TxD / KEY RxD / MSDATA / READY / REMOTE は 1 つの DIN コネクタに
  集約、ESD 保護 (TVS) を入れることを推奨 (TODO)

## 参考

- USB Type-C CC 1/2 ピンには 5.1kΩ プルダウン (VBUS / Source 認識のため必須)
- READY は X68000 起動時にしばらく Low のままなので、送信キューを内部に持つ
  実装を前提 (FW 側で対応済み)
- マウス機能を別基板に分けたい場合は、`functions/x68k_mouse/` を外して
  USART4 関連回路を不実装にし、コネクタも MSDATA を未配線にできる
- REMOTE (Pin 6) は X68000 純正キーボード上の TV リモコン受光部信号。
  当基板では PB8 GPIO に接続しておくだけで、用途は将来 FW 側で検討する

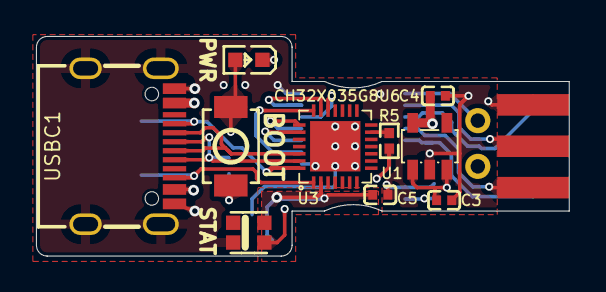
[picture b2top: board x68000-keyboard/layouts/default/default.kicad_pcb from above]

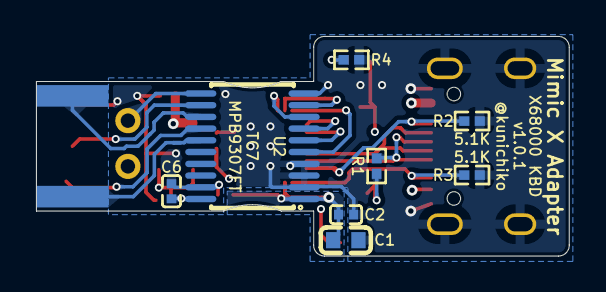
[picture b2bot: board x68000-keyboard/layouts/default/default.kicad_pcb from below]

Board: 4 copper layers, 29.6 x 12.2 mm, 19 parts (8 on the bottom side), 22 nets.

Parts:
C1: 4.7µF ±10%; C0603
C2, C5, C6: 100nF ±10%; C0402
C3, C4: 1µF ±10%; C0402
J1: MiniDIN_7P_X68000
LED1: LED0603-RD
LED2: LED-SMD_4P-L2.2-W2.0-P1.00_WS2815C-2020-4P
R1: 4.7kΩ ±1%; R0402
R2, R3: 5.1kΩ ±1%; R0402
R4: 1kΩ ±1%; R0402
R5: 470Ω ±1%; R0402
SW1: SW-SMD_L3.9-W3.0-P4.45
U1: SOT-23-5_L3.0-W1.7-P0.95-LS2.8-BR
U2: TSSOP-20_L6.5-W4.4-P0.65-LS6.5-BL
U3: QFN-28_L4.0-W4.0-P0.40-BL-EP2.8
USBC1: USB-C_SMD-TYPE-C-31-M-12_1

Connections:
GND: C1.2, C2.2, C3.2, C4.2, C5.2, C6.2, J1.7, LED2.2, R2.2, R3.2, R4.2, U1.2, U2.2, U2.3, U2.4, U2.10, U2.19, U3.29, USBC1.1, USBC1.2, USBC1.3, USBC1.4, USBC1.A1B12, USBC1.B1A12
KEY_RXD_3V3: U2.5, U3.21
KEY_TXD_3V3: U2.7, U3.22
MSDATA_3V3: U2.9, U3.20
PB0: R5.1, U3.13
PC14_CC1_T1C3_T2C2_: R2.1, U3.28, USBC1.A5
PC15_CC2_T2C3_T1ET_: R3.1, U3.1, USBC1.B5
READY_3V3: U2.6, U3.23
REMOTE_3V3: U2.8, U3.19
VBUS: C3.1, U1.1, U1.3, USBC1.A4B9, USBC1.B4A9
VCC2: C6.1, J1.1, U2.20
VDD33: C1.1, C2.1, C4.1, C5.1, LED1.2, LED2.4, SW1.1, U1.5, U2.1, U3.2
cathode: LED1.1, R4.1
din: LED2.3, R5.2
dn: U3.26, USBC1.A7, USBC1.B7
dp: R1.2, U3.27, USBC1.A6, USBC1.B6
key_rxd: J1.3, U2.15
key_txd: J1.4, U2.13
msdata: J1.2, U2.11
ready: J1.5, U2.14
remote: J1.6, U2.12
terminal_b: R1.1, SW1.2

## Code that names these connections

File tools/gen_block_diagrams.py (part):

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    s.line([(500, 550), (500, 610), (165, 610), (165, 660)])
    s.label(350, 604, ["VDD33 → SW1 → 4.7 kΩ → PC17 (USB D+)"])
    s.line([(690, 550), (690, 660)])
    s.label(702, 600, ["PB0 → 470 Ω → DIN"], anchor="start")

    s.panel(780, 640, 576, pin_heading, pin_rows, mono=True)
    s.legend(90, 900)
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            "PA2   RIGHT        →   pin 4",
            "PA6   TRIG-A       →   pin 6",
            "PA4   TRIG-B       →   pin 7",
            "PA0   COMMON / TH  ←   pin 8   MD 6-button select, TIM2_CH1",
            "      +5 V / GND       pin 5 / pin 9",
        ],
        notes_left=("Why the bus switch", [
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        conn_body=["X68000", "keyboard", "port"],
        lane_a="5 × 3.3 V",
        lane_b="5 × 5 V TTL",
        host_rail="VCCB = Vcc2 (DIN pin 1)",
        pin_heading="Pin map — CH32X035 ↔ bus switch ↔ mini DIN 7P",
        pin_rows=[
            "PB11  USART1_RX  ch6  ←  pin 4  KEY TxD   2400 8N1, host → kbd",
            "PB10  USART1_TX  ch4  →  pin 3  KEY RxD   2400 8N1, kbd → host",
            "PB12  GPIO in    ch5  ←  pin 5  READY     low blocks transmit",
            "PB9   USART4_TX  ch8  →  pin 2  MSDATA    4800 8N2, mouse",
            "PB8   GPIO       ch7  ↔  pin 6  REMOTE    TV remote line",
            "      +5 V / GND         pin 1 / pin 7  Vcc2, shield",
        ],
        notes_left=("Why the bus switch", [
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            "3 of the 8 channels are spare.",
        ]),
        notes_right=("Power domains", [
            "VBUS (USB) and Vcc2 (DIN pin 1)",
            "stay separate on the board, so",
            "nothing back-feeds when the",
            "phone and the X68000 are both",
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           stroke=PWR, sw=PWR_W)
    s.line([(1135, 630), (1065, 630)], stroke=PWR, sw=PWR_W)
    s.dot(1135, 630, PWR)
    s.label(640, 909, ["VCC_JOY (D-SUB pin 5) / VCC_KBD (DIN pin 1) "
                       "→ SS14 Schottky ×2 → VCC_ESP = XIAO 5 V pin"],
            color=PWR)

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    s.label(355, 741, ["SWD tap = the D4/D5 pair"], anchor="start")

    s.line([(700, 560), (700, 760)])
    s.label(712, 700, ["PB0 → 470 Ω → DIN"], anchor="start")

    s.line([(760, 390), (830, 390), (830, 320), (860, 320)], sw=BUS_W,
           arrow="both")
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
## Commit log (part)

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2026-05-01 Initial commit: Add README and .gitignore
2026-05-05 製品名「Mimic X」を README に追加
2026-05-07 デバッグLEDのピンを変更
2026-05-20 Update README with PCB layout links
    Added PCB layout links for ATARI joystick and X68000 keyboard adapters.
